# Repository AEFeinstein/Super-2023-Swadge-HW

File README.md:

# Super Magfest 2023 Swadge Hardware

## Welcome

This is the hardware repository for the Super Magfest 2022 Swadge.

The corresponding firmware repository for the Super Magfest 2023 Swadge [can be found here](https://github.com/AEFeinstein/Super-2023-Swadge-FW).

If you have any questions, feel free to create a Github ticket or email us at circuitboards@magfest.org.

## Render

## Schematic

## Directories

### `art`
This directory has the SVGs used to generate the KiCad files. The SVGs are drawn in [Inkscape](https://inkscape.org/) and exported with [Svg2Shenzhen](https://github.com/badgeek/svg2shenzhen)
### `3D-Print`
This directory has the 3D print files for the Swadge "Eggshell". 
### `SAOs/SAO1`
This directory has the design files for a Simple Add On shaped like Lil'B
### `shield`
This directory has the KiCad project for the PCB shield which protects the LEDs. 
### `shield_l`
This directory has the KiCad project for a test left-side shield which protects the LEDs. It was never manufacturered.
### `shield_r`
This directory has the KiCad project for a test right-side shield which protects the LEDs. It was never manufacturered.
### `Swadge-Parts`
This directory is a git submodule which has all the parts, footprints, and 3D models used in this project.
### `Swadge-S2-Devkit`
This directory has the KiCad project for the main Swadge PCB. It's not really a devkit anymore, but it started out as one!

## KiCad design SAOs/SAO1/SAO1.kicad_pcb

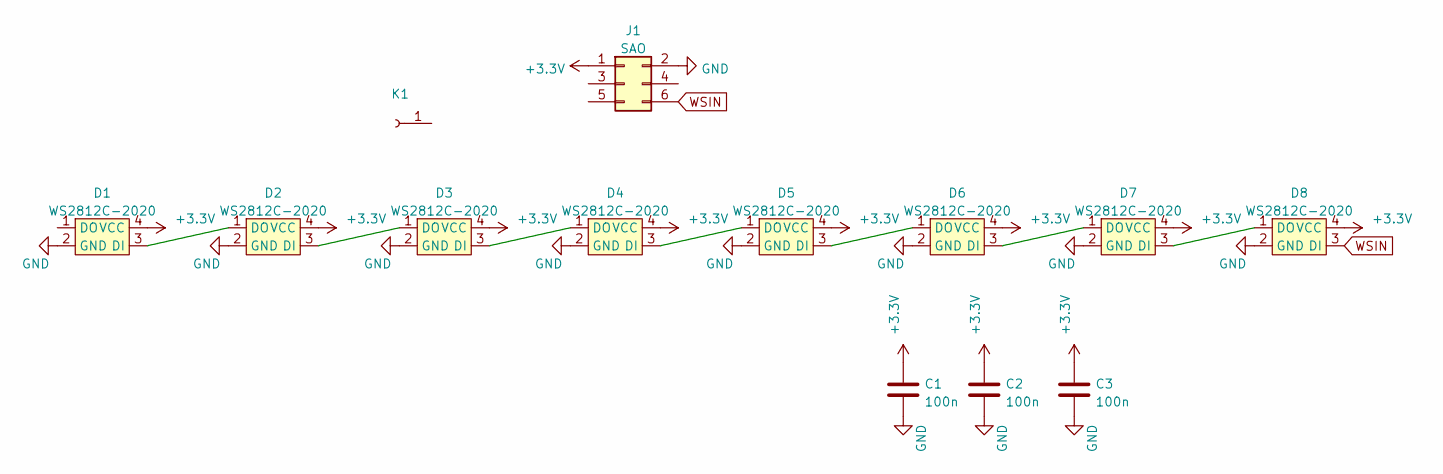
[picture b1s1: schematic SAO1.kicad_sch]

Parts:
C1, C2, C3: 100n; C_0603_1608Metric; LCSC C14663
D1, D2, D3, D4, D5, D6, D7, D8: WS2812C-2020; LCSC C2976072
J1: SAO; PinHeader_2x03_P2.54mm_Vertical; LCSC C65114
K1: bananaraptor

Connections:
+3.3V: C1.1, C2.1, C3.1, D1.4 (VCC), D2.4 (VCC), D3.4 (VCC), D4.4 (VCC), D5.4 (VCC), D6.4 (VCC), D7.4 (VCC), D8.4 (VCC), J1.1
GND: C1.2, C2.2, C3.2, D1.2 (GND), D2.2 (GND), D3.2 (GND), D4.2 (GND), D5.2 (GND), D6.2 (GND), D7.2 (GND), D8.2 (GND), J1.2
unnamed: D1.3 (DI), D2.1 (DO)
unnamed: D2.3 (DI), D3.1 (DO)
unnamed: D3.3 (DI), D4.1 (DO)
unnamed: D4.3 (DI), D5.1 (DO)
unnamed: D5.3 (DI), D6.1 (DO)
unnamed: D6.3 (DI), D7.1 (DO)
unnamed: D7.3 (DI), D8.1 (DO)
WSIN: D8.3 (DI), J1.6

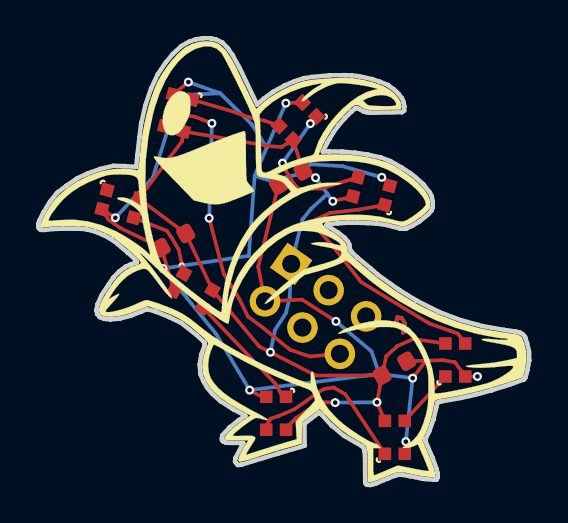
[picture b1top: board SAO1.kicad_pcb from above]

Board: 2 copper layers, 27.3 x 24.8 mm, 13 parts (1 on the bottom side), 10 nets.

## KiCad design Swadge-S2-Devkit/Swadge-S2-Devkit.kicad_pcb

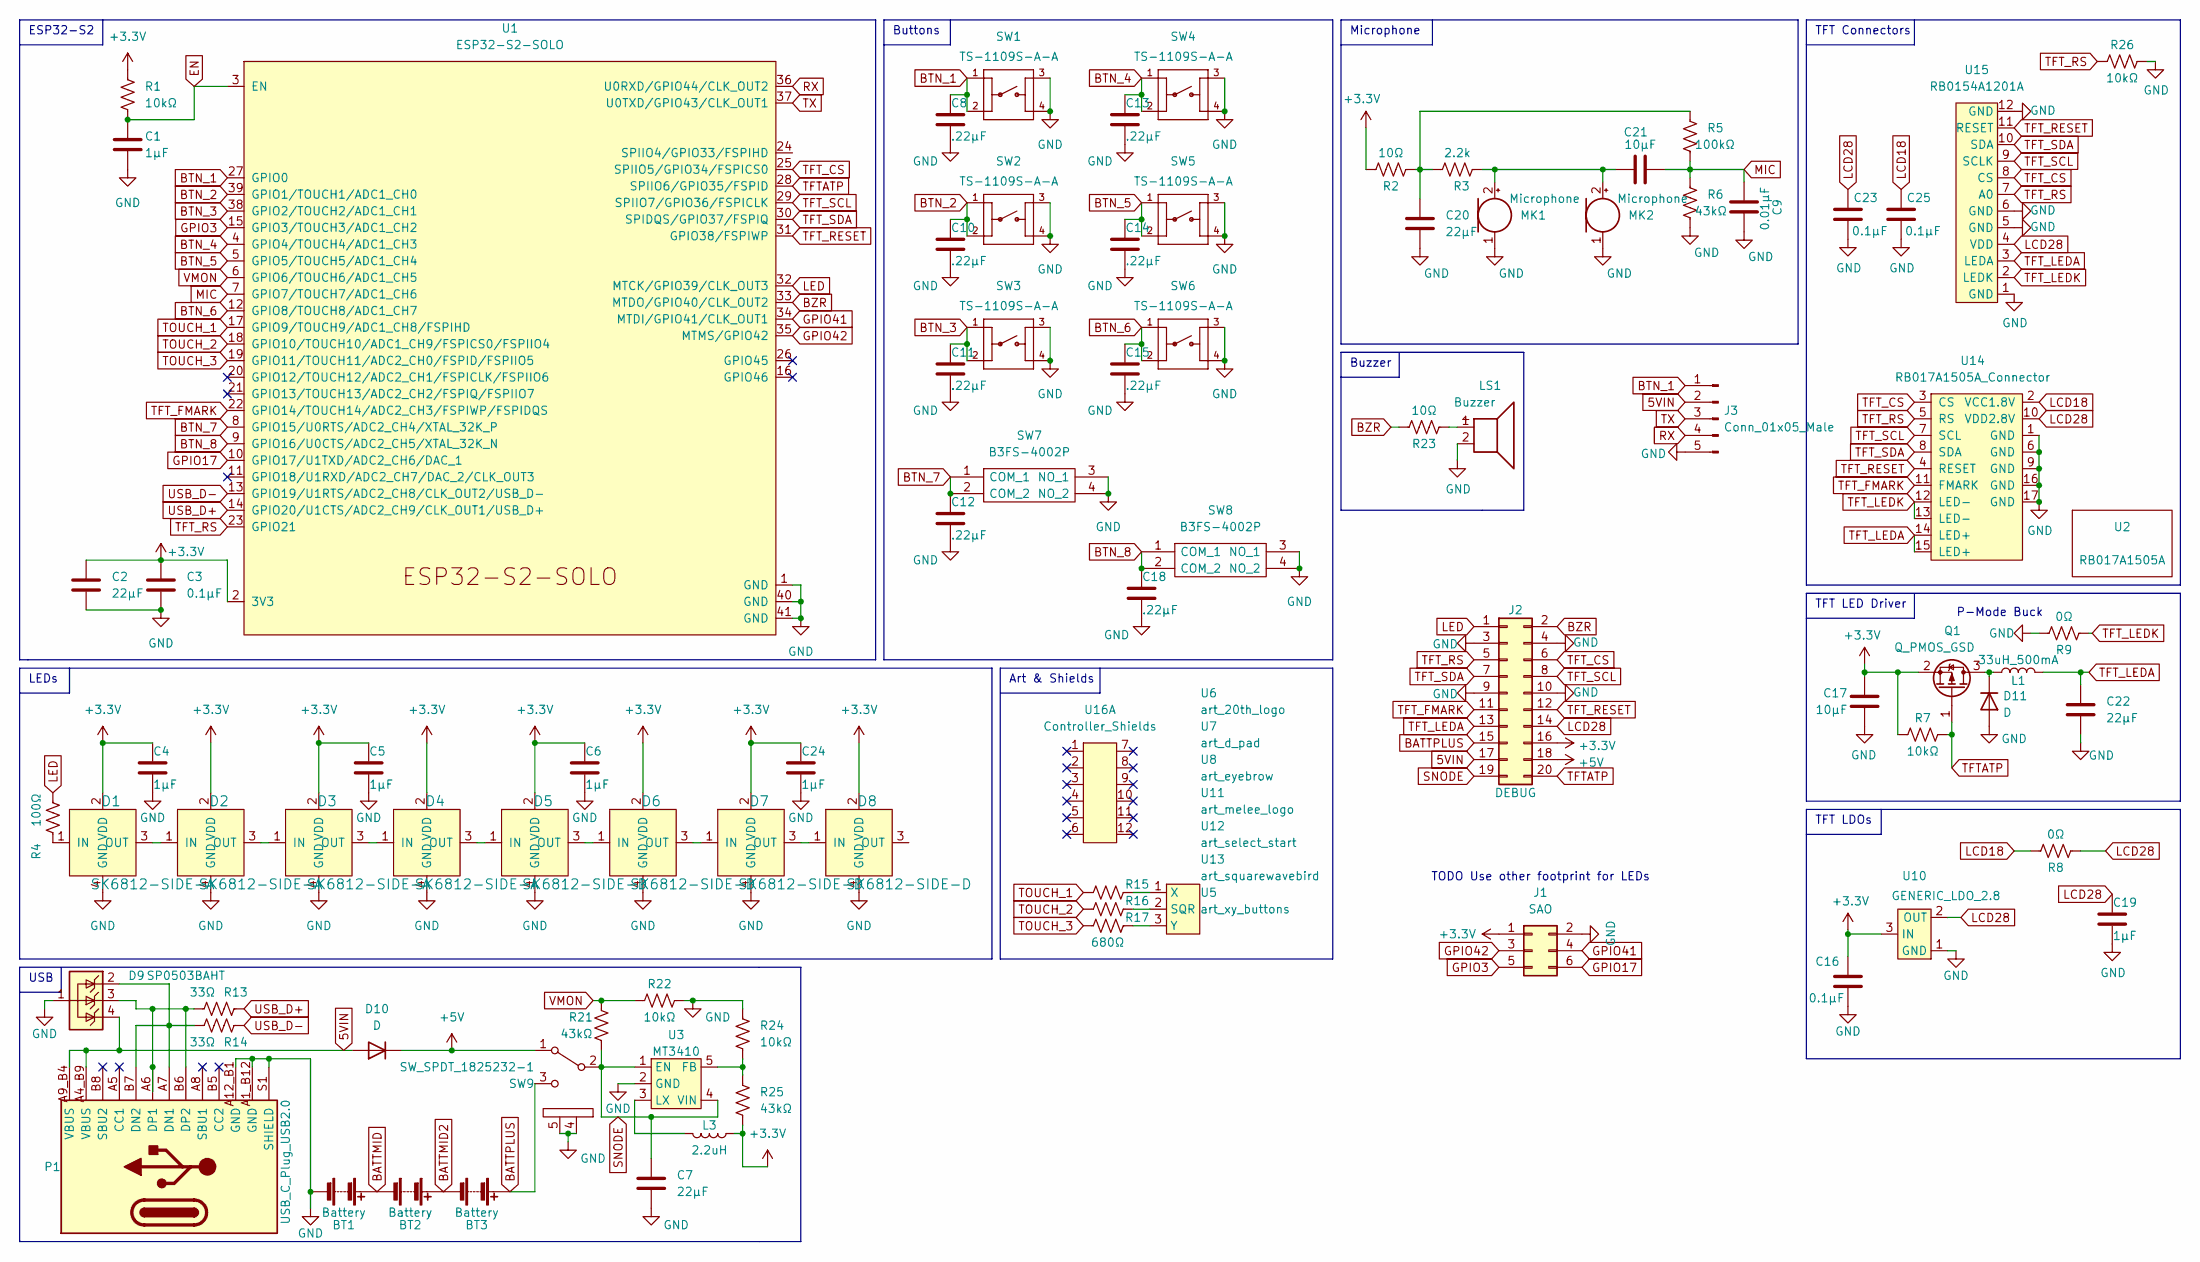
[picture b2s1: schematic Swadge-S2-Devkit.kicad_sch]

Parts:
BT1, BT2, BT3: Battery; 2460; Digikey 36-2460-ND
C1, C4, C5, C6, C19, C24: 1μF; C_0603_1608Metric; LCSC C1592
C2, C7, C20, C22: 22μF; C_0603_1608Metric; LCSC C86295
C3, C16, C23, C25: 0.1μF; C_0603_1608Metric; LCSC C282519
C8, C10, C11, C12, C13, C14, C15, C18: .22μF; C_0603_1608Metric; LCSC C21120
C9: 0.01μF; C_0603_1608Metric; LCSC C14663
C17, C21: 10μF; C_0603_1608Metric; LCSC C96446
D1, D2, D3, D4: SK6812-SIDE-A; SK6812_SIDE_2; Digikey 1528-4691-ND
D5, D6, D7, D8: SK6812-SIDE-D; SK6812D_SIDE; Digikey 2007-BB-HRGB24R-TRB-BTR-ND
D9: SP0503BAHT; SOT-143; Digikey F2715CT-ND
D10, D11: D; D_SMA; Digikey 2616-GS1J-ND
J1: SAO; PinSocket_2x03_P2.54mm_Vertical; LCSC N/A
J2: DEBUG; PinHeader_2x10_P2.54mm_Vertical; LCSC C492427
J3: Conn_01x05_Male; PinHeader_1x05_P2.54mm_Vertical; LCSC C390683
L1: 33uH_500mA; L_1210_3225Metric; LCSC C90317
L3: 2.2uH; L_1008_2520Metric; LCSC C216158
LS1: Buzzer; Buzzer_12.5x7.5; LCSC C219727
MK1: Microphone; INGHAi GMI6050P-56DB; Digikey 102-1721-ND
MK2: Microphone; GOERTEK_MIC_B4013AM423; LCSC C2835889
P1: USB_C_Plug_USB2.0; USB_C_Receptacle_HRO_TYPE-C-31-M-12; LCSC C2765186
Q1: Q_PMOS_GSD; SOT-23; LCSC C2763847
R1, R7, R22, R24, R26: 10kΩ; R_0603_1608Metric; LCSC C25197
R2, R23: 10Ω; R_0603_1608Metric; LCSC C22859
R3: 2.2k; R_0603_1608Metric; LCSC C4190
R4: 100Ω; R_0603_1608Metric; LCSC C22936
R5: 100kΩ; R_0603_1608Metric; LCSC C22936
R6, R21, R25: 43kΩ; R_0603_1608Metric; LCSC C23172
R8, R9: 0Ω; R_0603_1608Metric; LCSC C21189
R13, R14: 33Ω; R_0603_1608Metric; LCSC C23140
R15, R16, R17: 680Ω; R_0603_1608Metric; LCSC C23228
SW1, SW2, SW3, SW4, SW5, SW6: TS-1109S-A-A; SW_4-1437565-2; Digikey 2223-TS04-66-65-BK-100-SMT-ND
SW7, SW8: B3FS-4002P; B3FS4002P; Digikey SW1278CT-ND
SW9: SW_SPDT_1825232-1; 1825232-1; Digikey A107673-ND
U1: ESP32-S2-SOLO; Digikey 1965-ESP32-S2-SOLO-N4R2TR-ND
U2: RB017A1505A; NULL
U3: MT3410; SOT-23-5; LCSC C883494
U5: art_xy_buttons; XY_Buttons
U6: art_20th_logo; 20th_Logo
U7: art_d_pad; d-pad
U8: art_eyebrow; eyebrow
U10: GENERIC_LDO_2.8; SOT-23; LCSC C347374
U11: art_melee_logo; Melee_Logo
U12: art_select_start; select-start
U13: art_squarewavebird; squarewavebird
U14: RB017A1505A_Connector; HCTL HC-FPC-03-10-15RLTAG; Digikey A141392TR-ND
U15: RB0154A1201A; LCD_240x240_1.54_12
U16: Controller_Shields; shields; LCSC C124375

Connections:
5VIN: D9.4 (K), D10.2 (A), J2.17, J3.2, P1.A4_B9 (VBUS), P1.A9_B4 (VBUS)
+3V3: C2.1, C3.1, C4.1, C5.1, C6.1, C16.1, C17.1, C24.1, D1.2 (VDD), D2.2 (VDD), D3.2 (VDD), D4.2 (VDD), D5.2 (VDD), D6.2 (VDD), D7.2 (VDD), D8.2 (VDD), J1.1, J2.16, L3.1, Q1.2 (S), R1.1, R2.1, R7.1, R25.2, U1.2 (3V3), U10.3 (IN)
+5V: D10.1 (K), J2.18, SW9.1 (A)
BATTMID: BT1.1 (+), BT2.2 (-)
BATTMID2: BT2.1 (+), BT3.2 (-)
BATTPLUS: BT3.1 (+), J2.15, SW9.3 (C)
BTN_1: C8.1, J3.1, SW1.1, SW1.2, U1.27 (GPIO0)
BTN_2: C10.1, SW2.1, SW2.2, U1.39 (GPIO1/TOUCH1/ADC1_CH0)
BTN_3: C11.1, SW3.1, SW3.2, U1.38 (GPIO2/TOUCH2/ADC1_CH1)
BTN_4: C13.1, SW4.1, SW4.2, U1.4 (GPIO4/TOUCH4/ADC1_CH3)
BTN_5: C14.1, SW5.1, SW5.2, U1.5 (GPIO5/TOUCH5/ADC1_CH4)
BTN_6: C15.1, SW6.1, SW6.2, U1.12 (GPIO8/TOUCH8/ADC1_CH7)
BTN_7: C12.1, SW7.1 (COM_1), SW7.2 (COM_2), U1.8 (GPIO15/U0RTS/ADC2_CH4/XTAL_32K_P)
BTN_8: C18.1, SW8.1 (COM_1), SW8.2 (COM_2), U1.9 (GPIO16/U0CTS/ADC2_CH5/XTAL_32K_N)
BZR: J2.2, R23.1, U1.33 (MTDO/GPIO40/CLK_OUT2)
EN: C1.1, R1.2, U1.3 (EN)
GND: BT1.2 (-), C1.2, C2.2, C3.2, C4.2, C5.2, C6.2, C7.2, C8.2, C9.1, C10.2, C11.2, C12.2, C13.2, C14.2, C15.2, C16.2, C17.2, C18.2, C19.2, C20.2, C22.2, C23.2, C24.2, C25.2, D1.4 (GND), D2.4 (GND), D3.4 (GND), D4.4 (GND), D5.4 (GND), D6.4 (GND), D7.4 (GND), D8.4 (GND), D9.1 (A), D11.2 (A), J1.2, J2.3, J2.4, J2.9, J2.10, J3.5, LS1.2, MK1.1 (-), MK2.1 (-), P1.A1_B12 (GND), P1.A12_B1 (GND), P1.S1 (SHIELD), R6.2, R9.1, R22.2, R24.1, R26.2, SW1.3, SW1.4, SW2.3, SW2.4, SW3.3, SW3.4, SW4.3, SW4.4, SW5.3, SW5.4, SW6.3, SW6.4, SW7.3 (NO_1), SW7.4 (NO_2), SW8.3 (NO_1), SW8.4 (NO_2), SW9.4 (D), SW9.5 (E), U1.1 (GND), U1.40 (GND), U1.41 (GND), U3.2 (GND), U10.1 (GND), U14.1 (GND), U14.6 (GND), U14.9 (GND), U14.16 (GND), U14.17 (GND), U15.1 (GND), U15.5 (GND), U15.6 (GND), U15.12 (GND)
GPIO3: J1.5, U1.15 (GPIO3/TOUCH3/ADC1_CH2)
GPIO17: J1.6, U1.10 (GPIO17/U1TXD/ADC2_CH6/DAC_1)
GPIO41: J1.4, U1.34 (MTDI/GPIO41/CLK_OUT1)
GPIO42: J1.3, U1.35 (MTMS/GPIO42)
LCD18: C25.1, R8.1, U14.2 (VCC1.8V)
LCD28: C19.1, C23.1, J2.14, R8.2, U10.2 (OUT), U14.10 (VDD2.8V), U15.4 (VDD)
LED: J2.1, R4.1, U1.32 (MTCK/GPIO39/CLK_OUT3)
MIC: C9.2, C21.2, R5.2, R6.1, U1.7 (GPIO7/TOUCH7/ADC1_CH6)
unnamed: C20.1, R2.2, R3.1, R5.1
unnamed: C21.1, MK1.2 (+), MK2.2 (+), R3.2
unnamed: D1.1 (IN), R4.2
unnamed: D1.3 (OUT), D2.1 (IN)
unnamed: D2.3 (OUT), D3.1 (IN)
unnamed: D3.3 (OUT), D4.1 (IN)
unnamed: D4.3 (OUT), D5.1 (IN)
unnamed: D5.3 (OUT), D6.1 (IN)
unnamed: D6.3 (OUT), D7.1 (IN)
unnamed: D7.3 (OUT), D8.1 (IN)
unnamed: D9.3 (K), P1.A6 (DP1), P1.B6 (DP2), R13.2
unnamed: D11.1 (K), L1.1, Q1.3 (D)
unnamed: L3.2, U3.3 (LX)
unnamed: LS1.1, R23.2
unnamed: D9.2 (K), P1.A7 (DN1), P1.B7 (DN2), R14.2
unnamed: R15.1, U5.1 (X)
unnamed: R16.1, U5.2 (SQR)
unnamed: R17.1, U5.3 (Y)
unnamed: R24.2, R25.1, U3.5 (FB)
RX: J3.4, U1.36 (U0RXD/GPIO44/CLK_OUT2)
SNODE: C7.1, J2.19, R21.2, SW9.2 (B), U3.1 (EN), U3.4 (VIN)
TFTATP: J2.20, Q1.1 (G), R7.2, U1.28 (SPIIO6/GPIO35/FSPID)
TFT_CS: J2.6, U1.25 (SPIIO5/GPIO34/FSPICS0), U14.3 (CS), U15.8 (CS)
TFT_FMARK: J2.11, U1.22 (GPIO14/TOUCH14/ADC2_CH3/FSPIWP/FSPIDQS), U14.11 (FMARK)
TFT_LEDA: C22.1, J2.13, L1.2, U14.14 (LED+), U14.15 (LED+), U15.3 (LEDA)
TFT_LEDK: R9.2, U14.12 (LED-), U14.13 (LED-), U15.2 (LEDK)
TFT_RESET: J2.12, U1.31 (GPIO38/FSPIWP), U14.4 (RESET), U15.11 (RESET)
TFT_RS: J2.5, R26.1, U1.23 (GPIO21), U14.5 (RS), U15.7 (A0)
TFT_SCL: J2.8, U1.29 (SPIIO7/GPIO36/FSPICLK), U14.7 (SCL), U15.9 (SCLK)
TFT_SDA: J2.7, U1.30 (SPIDQS/GPIO37/FSPIQ), U14.8 (SDA), U15.10 (SDA)
TOUCH_1: R15.2, U1.17 (GPIO9/TOUCH9/ADC1_CH8/FSPIHD)
TOUCH_2: R16.2, U1.18 (GPIO10/TOUCH10/ADC1_CH9/FSPICS0/FSPIIO4)
TOUCH_3: R17.2, U1.19 (GPIO11/TOUCH11/ADC2_CH0/FSPID/FSPIIO5)
TX: J3.3, U1.37 (U0TXD/GPIO43/CLK_OUT1)
USB_D+: R13.1, U1.14 (GPIO20/U1CTS/ADC2_CH9/CLK_OUT1/USB_D+)
USB_D-: R14.1, U1.13 (GPIO19/U1RTS/ADC2_CH8/CLK_OUT2/USB_D-)
VMON: R21.1, R22.1, U1.6 (GPIO6/TOUCH6/ADC1_CH5)

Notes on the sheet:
TFT LDOs
P-Mode Buck
Art & Shields
Buttons
ESP32-S2
Microphone
LEDs
TODO Use other footprint for LEDs
TFT LED Driver
TFT Connectors
USB
Buzzer

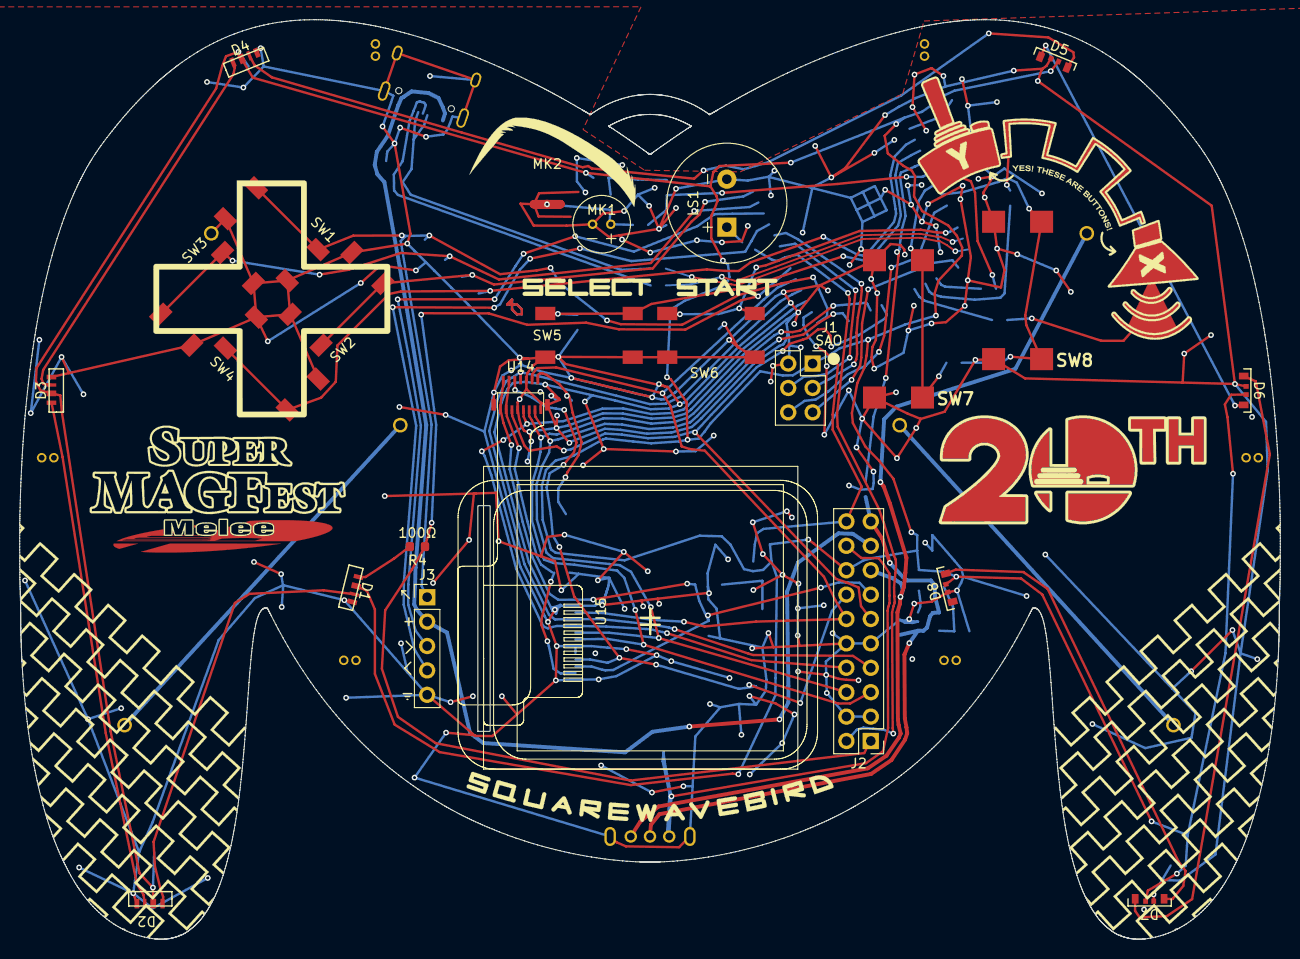
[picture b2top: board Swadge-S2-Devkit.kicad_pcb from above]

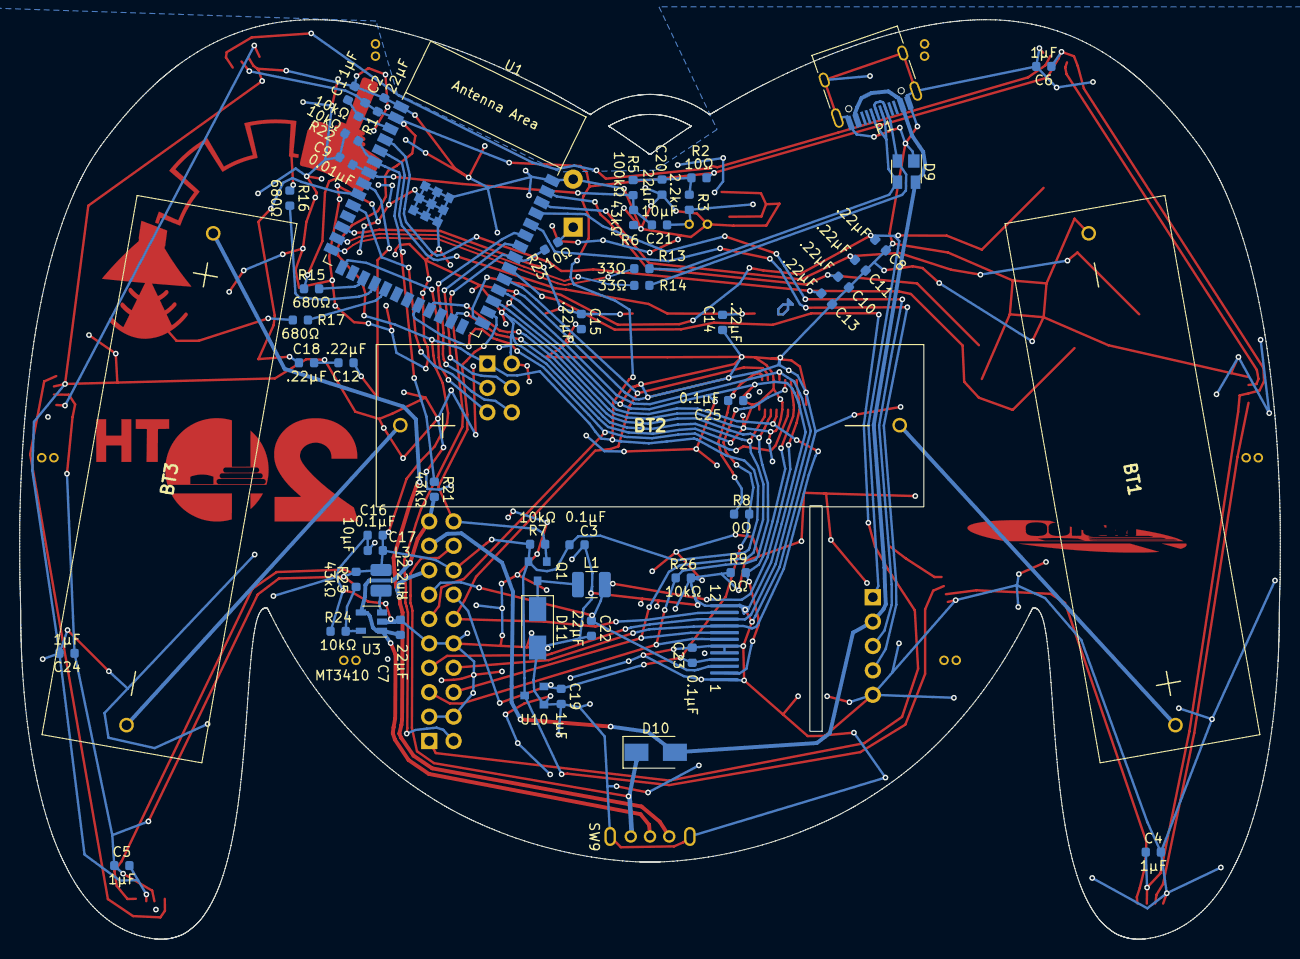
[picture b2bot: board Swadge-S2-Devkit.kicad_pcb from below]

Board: 2 copper layers, 131.2 x 95.7 mm, 93 parts (58 on the bottom side), 62 nets.

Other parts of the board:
Ref**: Val**; Controller_Shape

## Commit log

2021-12-27 Added project, swadge parts submodule
2021-12-27 Added ESP32 and board outline
2021-12-31 Worked on schematic and layout
2022-01-02 Added more to schematic
2022-01-03 Added TFT, vib motor
2022-01-05 Updated layout
2022-01-06 Updated PCB
2022-01-13 Connected PCIe, replaced S3 with S2, cleanup
2022-01-14 Added diodes to USB, added pin headers, cleaned schematic
2022-01-14 Added missing label
2022-01-14 Update peripherals and library.
2022-01-19 Working on devkit, progress.
2022-01-19 Bump rev.
2022-01-20 Update with routing.
2022-01-22 Update design.
2022-01-24 Bump
2022-01-28 bump schematic notes
2022-04-04 Bump with design changes + devkit footprints
2022-04-05 Update deisgn and bump parts
2022-04-07 Update with new LCDs
2022-04-11 Bump design with new LCDs, etc.
2022-04-11 Bump - with bigger outline
2022-04-13 Bump with routing
2022-04-20 Update as initial rev -
2022-05-05 Removed unused parts of schematic. Replaced out of stock parts. Rerouted batteries, LDOs
2022-05-05 Fix footprint
2022-05-06 Fixed all import and DRC errors. Cleaned up BOM
2022-05-07 Switch inductors, fix warnings
2022-05-08 Fixed warnings
2022-05-09 Update note for manufacturing Add silkscreen version Ignore output folder
2022-07-24 Connect DP2 and DN2 on USB-C connector
2022-07-24 Remove accelerometer
2022-07-24 Removed speaker
2022-07-24 Removed vibration motor
2022-07-24 Removed edge and pin connectors
2022-07-24 Reduced to six pushbuttons
2022-07-24 Fix power schematic
2022-07-24 Clean up power schematic
2022-07-24 Replaced slide switch
2022-07-24 Added new tactile switches
2022-07-24 Reset PCB
2022-07-24 Added note for AA holder
2022-07-24 Replaced touch wheel with start/select
2022-07-27 Updated buttons, LEDs, TFTs for prototype
2022-07-28 Started prototype part placement
2022-07-29 Added shields projects. Updated main PCB
2022-07-29 Added LCSC part numbers, cleanup
2022-07-29 Fixed footprints and models for mic, bzr, slide switch, SK6812
2022-07-29 Added correct FPC connector footprint
2022-07-30 Replaced shield_r/l with shield project. Added art files
2022-07-31 Removed auto backup
2022-08-01 Update submodule
2022-08-01 Update main board
2022-08-01 update design
2022-08-02 Cleaned up part references, BOM
2022-08-03 Update design, routed.
2022-08-03 Clean BOM, update designators, move passives from under batteries, flip mic positions, use parts in Swadge_Parts
2022-08-03 Readded accel
2022-08-03 Adjusted mic positions, removed SAO connections
2022-08-04 Removed 20 pin monstrosity, rerouted
2022-08-04 Bump swadge.
2022-08-05 Point Swadge-Parts at actual ref
2022-08-05 Update kidneys from library
2022-08-05 Moved battery lower. Placed SAO
2022-08-05 * Add Slider (remove center touch) * Route board
2022-08-05 Forgot to update schematic to reflect change with touch sensor.
2022-08-05 Flipped SAO to back, added more battery clearance
2022-08-05 Use C 1210 from Swadge-Parts
2022-08-05 Added curved touch bar chevrons art
2022-08-05 Place and route touch bar
2022-08-09 fix LCSC part number
2022-08-09 Update to EV1
2022-08-09 Commit from ev1order branch directly to main
2022-08-09 Updated footprint for SK6812-side-A, rerouted to match
2022-08-09 Replaced 4.5mm tact switch with 6mm tact switch, rerouted
2022-08-09 Update button values
2022-08-09 Replaced 6mm buttons with 4.5mm buttons
2022-08-10 Bump - But it doesn't look like we'll be able to switch the order.
2022-08-14 Actual bump to EV1.
2022-08-15 Update as ordered.
2022-08-17 Add submitted order.
2022-08-24 Add a test SAO
2022-08-24 Update swadge-parts
2022-08-31 Put squarewave art on shields
2022-09-04 Added silkscreen for touch slider
2022-09-04 Ignore backups
2022-09-04 Moved power switch upwards, added silkscreen
2022-09-04 added URL and email silkscreen
2022-09-04 Added silkscreen for A & B buttons
2022-09-04 Added programming button indicator, version silk
2022-09-04 Embiggen holes on shield, remove standoff capacitors, tie all standoff pins to GND
2022-09-04 Flipped, moved, and DNP'd the SAO connector
2022-09-05 Move screen up, move start & select down, route GND between SCL and SDA
2022-09-05 Remove debounce caps
2022-09-05 Use correct footprint for SAO
2022-09-05 Update design to resolve more issues. Notably fixing USB + microphone circuitry and removing designators, and flipping programming header to back-only.
2022-09-05 Add designators under parts, remove extra text, clean silkscreen
2022-09-05 Tweak export for sheilds
2022-09-06 added projects for L&R shields with metal bottoms
2022-09-06 Exported gerbers
2022-09-06 Added paste layers
2022-09-06 Update to EV2(a)
2022-09-06 EV2-B (with LEDs next to buttons, avoiding hats)
2022-09-10 Ok actually go with EV2C
2022-09-14 Add metal to sheilds
2022-09-16 Add CAD for all parts
2022-09-22 * Remove 0 ohm resistors (by shorting them through) * Convert 10u to 22u * Fix header LCSC Part # * Add note about nopop on SAO header * Remove dangling 3.3v rail
2022-09-22 Update battery & menu silk
2022-09-22 Add CAD parts
2022-09-22 Fix warnings
2022-09-23 Updated version
2022-09-24 Better curve SQUAREWAVEBIRD text
2022-09-25 Added back-menu art
2022-09-25 Added dpad flourish art
2022-09-26 Add xy_sqwv art
2022-09-26 Add ab_magnificent art
2022-09-26 Add select_start_menu art
2022-09-26 add mmxxiii art
2022-09-26 Add text
2022-09-26 Resize logos, add to back
2022-09-27 Split dpad-flourish into 20th anniv, vertically aligned front logos
2022-09-27 Curved xy_sqwv more
2022-09-27 Added SAO dot
2022-09-27 Release for MP1
2022-10-17 Replace all SK6812D_SIDE footprints with SK6812_SIDE_2 footprints. DID NOT REROUTE. DRC FAILS!
2022-10-17 Move to MP2, routing the traces from last commit + Making gerber package + fix gap in track.
2022-10-17 Fix more warnings, clean up more traces
2022-10-17 Build out mp2 again
2022-10-27 Add silk outline for display, increment version
2022-10-29 Updated back menu art, version silk, url & email
2022-10-30 Update with MP3 - validated all changes from MP2.
2022-11-09 Add part for shield art
2022-11-29 Add 3d prints
    Add 3d print folder, updated readme, uploaded latest STLs for FDM and SLA
2022-11-30 Update Eggshell_front_FDM
    Deleted offset face
2022-11-30 Revert "Update Eggshell_front_FDM"
    This reverts commit 3d3f6df7c45eaf464af25f82c164def461878c8d.
2022-11-30 repair FDM variant
    deleted offset face
2022-11-30 Update Eggshell_front_FDM.STL
    repair inner faces to make parallel
2022-12-02 Update Eggshell_back_SLA.STL
    changed mounting hole for threaded insert
2022-12-02 Create README.txt
    3D print instructions
2022-12-02 Revert "Create README.txt"
    This reverts commit 6a87dede479de5b7a505e1a2c1f0bb8519aff145.
2022-12-02 Create README.md
    3d print instructions
2022-12-02 Update README.md
    added CC licensing and adjusted formatting issues
2022-12-02 render image
    add render, clean up readme formatting
2022-12-08 renders
2022-12-08 readme updates, render uploads
